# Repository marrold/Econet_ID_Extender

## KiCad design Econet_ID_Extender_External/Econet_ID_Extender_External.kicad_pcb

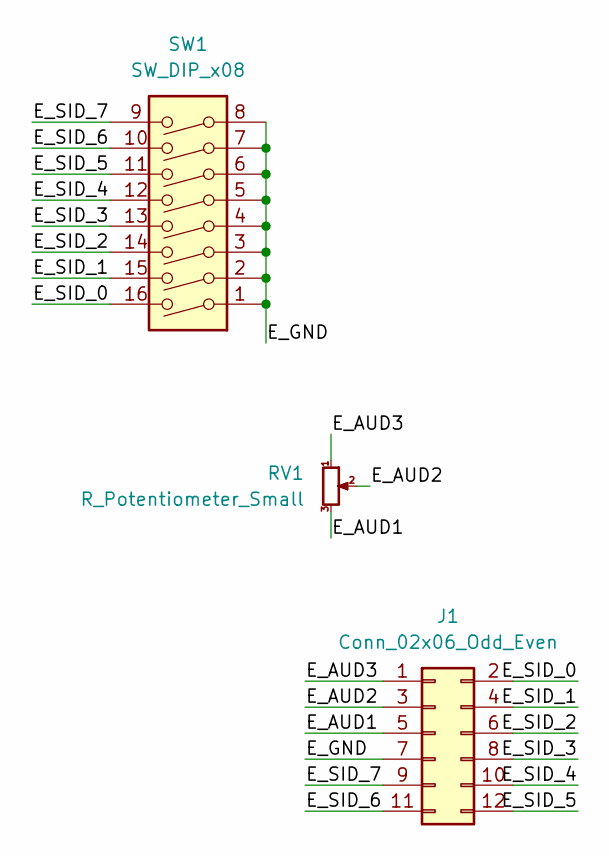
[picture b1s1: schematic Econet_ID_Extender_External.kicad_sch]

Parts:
J1: Conn_02x06_Odd_Even; PinHeader_2x06_P2.54mm_Vertical_SMD
RV1: R_Potentiometer_Small; Potentiometer_Bourns_3386P_Vertical
SW1: SW_DIP_x08; DIP-16_W7.62mm

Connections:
/E_AUD1: J1.5, RV1.3
/E_AUD2: J1.3, RV1.2
/E_AUD3: J1.1, RV1.1
/E_GND: J1.7, SW1.1, SW1.2, SW1.3, SW1.4, SW1.5, SW1.6, SW1.7, SW1.8
/E_SID_0: J1.2, SW1.16
/E_SID_1: J1.4, SW1.15
/E_SID_2: J1.6, SW1.14
/E_SID_3: J1.8, SW1.13
/E_SID_4: J1.10, SW1.12
/E_SID_5: J1.12, SW1.11
/E_SID_6: J1.11, SW1.10
/E_SID_7: J1.9, SW1.9

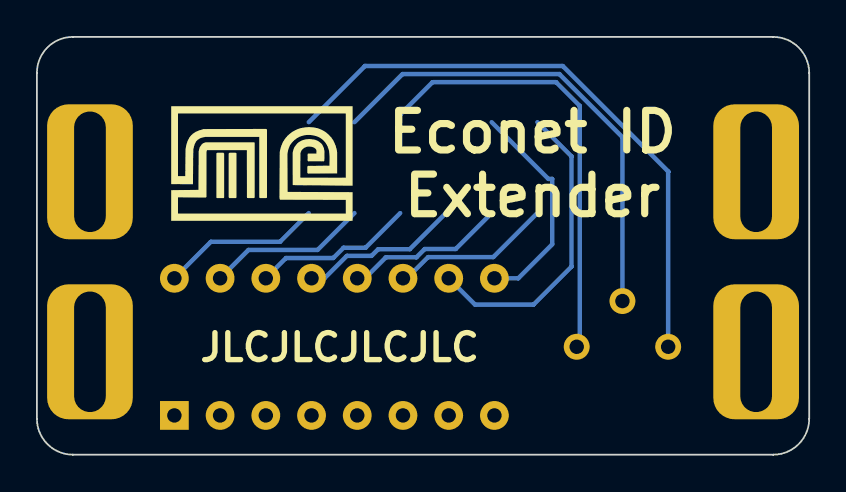
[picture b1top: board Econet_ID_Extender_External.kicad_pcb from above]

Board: 2 copper layers, 42.9 x 23.2 mm, 3 parts (1 on the bottom side), 12 nets.

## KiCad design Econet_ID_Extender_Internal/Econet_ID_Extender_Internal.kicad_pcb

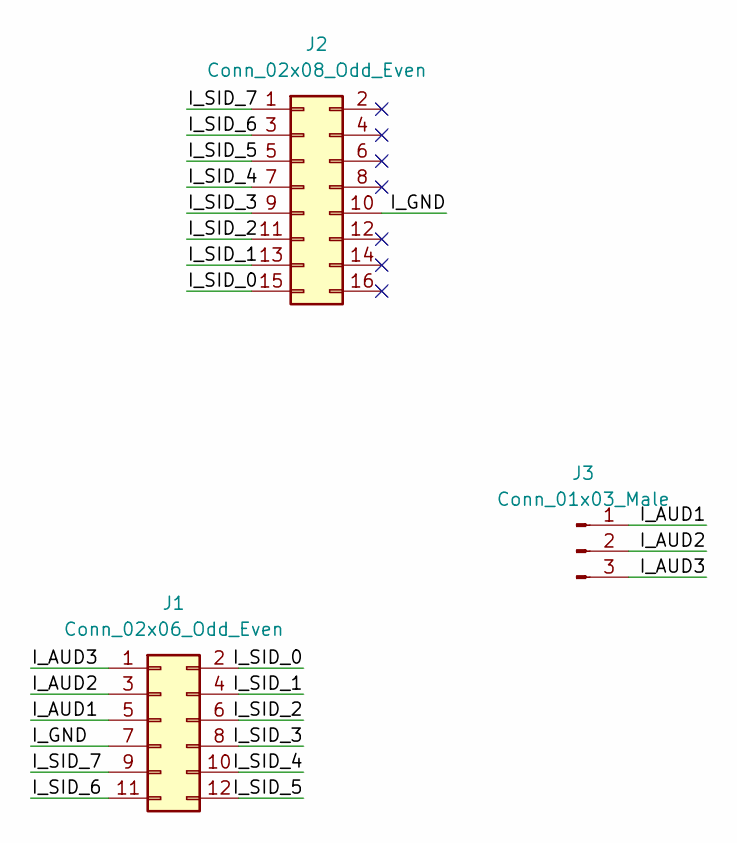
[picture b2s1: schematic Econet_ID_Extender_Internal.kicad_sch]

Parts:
J1: Conn_02x06_Odd_Even; IDC-Header_2x06_P2.54mm_Vertical_SMD
J2: Conn_02x08_Odd_Even; PinSocket_2x08_P2.54mm_Vertical_SMD
J3: Conn_01x03_Male; PinHeader_1x03_P2.54mm_Horizontal

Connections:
/I_AUD1: J1.5, J3.1
/I_AUD2: J1.3, J3.2
/I_AUD3: J1.1, J3.3
/I_GND: J1.7, J2.10
/I_SID_0: J1.2, J2.15
/I_SID_1: J1.4, J2.13
/I_SID_2: J1.6, J2.11
/I_SID_3: J1.8, J2.9
/I_SID_4: J1.10, J2.7
/I_SID_5: J1.12, J2.5
/I_SID_6: J1.11, J2.3
/I_SID_7: J1.9, J2.1

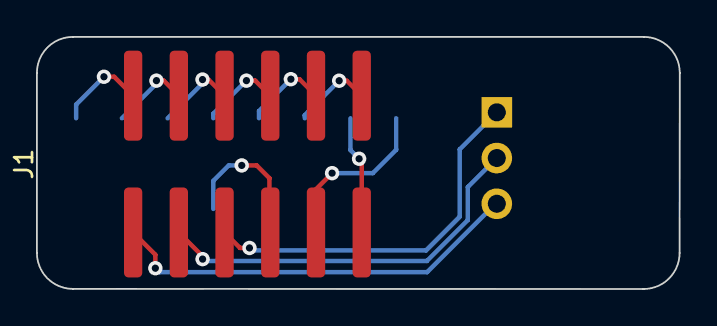
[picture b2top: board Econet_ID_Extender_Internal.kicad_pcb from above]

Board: 2 copper layers, 35.7 x 14.0 mm, 3 parts (1 on the bottom side), 12 nets.

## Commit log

2024-01-04 init
2024-01-04 Rename Econet_ID_Extender_External.pretty
2024-01-05 Swap to standard 2.54 pitch ribbon
2024-01-05 Add repo to silkscreen
2024-01-05 Rename Library
2024-01-05 Add Gerbers
2024-01-24 Fix volume pot orientation
